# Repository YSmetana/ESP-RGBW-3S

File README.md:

View this project on [CADLAB.io](https://cadlab.io/project/24320). 

# ESP-RGBW-3S
## Soldering
### Special
R91-R94 used only if GPIO12-14 are using as pins which needs pull-up resistors. In this case R11-18 should not be used.

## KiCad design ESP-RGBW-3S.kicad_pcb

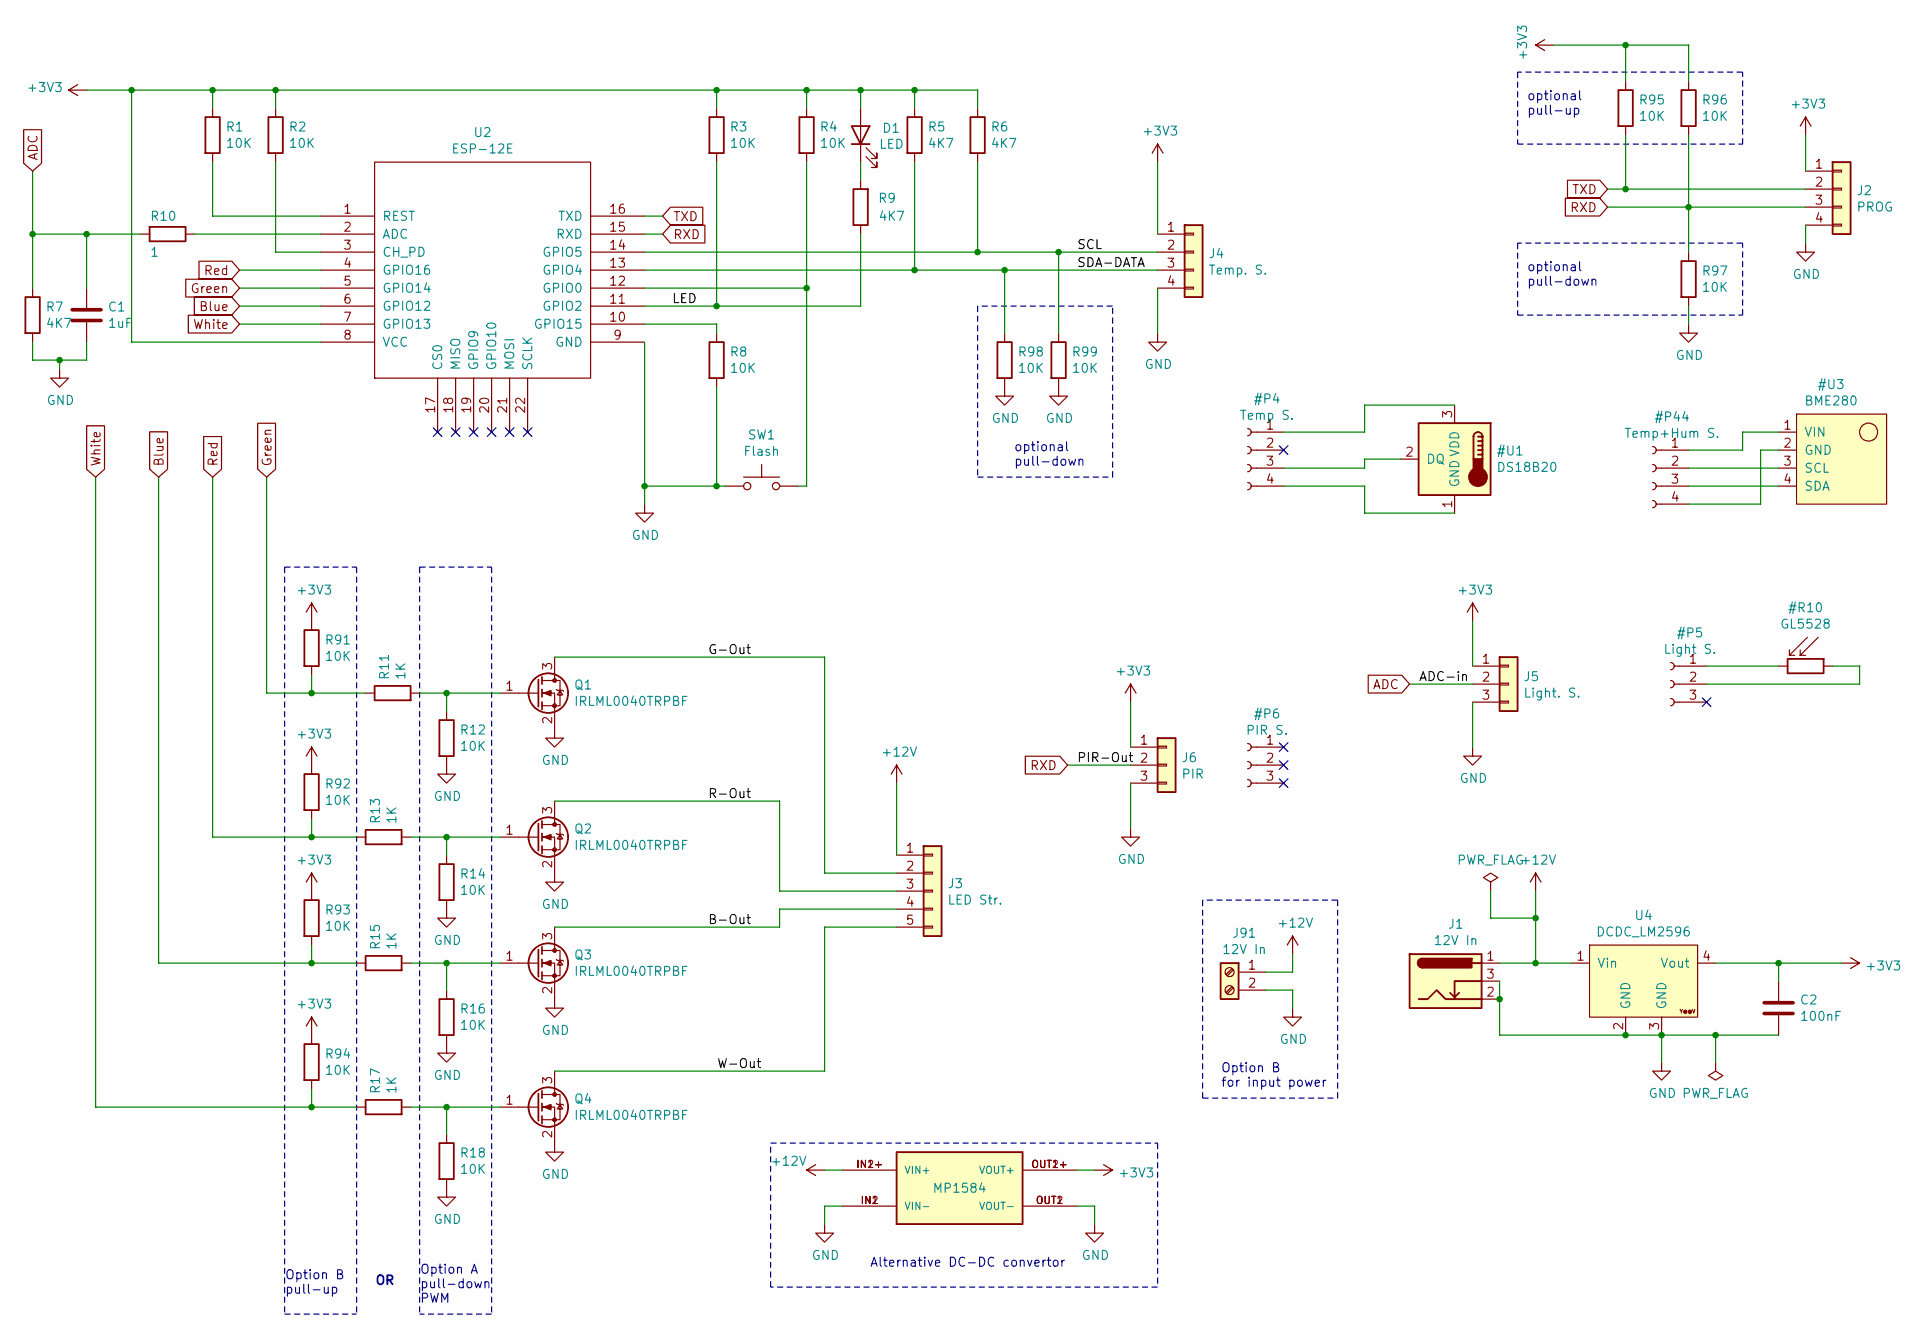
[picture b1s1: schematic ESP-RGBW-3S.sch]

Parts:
C1: 1uF; C_0805_2012Metric
C2: 100nF; C_0805_2012Metric
D1: LED; LED_D1.8mm_W3.3mm_H2.4mm
J1: 12V In; BarrelJack_Horizontal
J2: PROG; PinHeader_1x04_P2.54mm_Vertical
J3: LED Str.; Molex_KK-254_AE-6410-05A_1x05_P2.54mm_Vertical
J4: Temp. S.; Molex_KK-254_AE-6410-04A_1x04_P2.54mm_Vertical
J5: Light. S.; Molex_KK-254_AE-6410-03A_1x03_P2.54mm_Vertical
J6: PIR; Molex_KK-254_AE-6410-03A_1x03_P2.54mm_Vertical
J91: 12V In; TerminalBlock_Phoenix_MKDS-1,5-2_1x02_P5.00mm_Horizontal
Q1, Q2, Q3, Q4: IRLML0040TRPBF; SOT-23
R1, R2, R3, R4, R8, R12, R14, R16, R18, R91, R92, R93, R94, R95, R96, R97, R98, R99: 10K; R_0805_2012Metric
R5, R6, R7, R9: 4K7; R_0805_2012Metric
R10: 1; R_0805_2012Metric
R11, R13, R15, R17: 1K; R_0805_2012Metric
SW1: Flash; SW_Push_SPST_NO_Alps_SKRK
U2: ESP-12E; ESP-12E_SMD
U4: DCDC_LM2596; YAAJ_DCDC_StepDown_LM2596
U94: MP1584; DC-BRICK

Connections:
+3V3: C2.1, D1.2 (A), J2.1, J4.1, J5.1, J6.1, R1.1, R2.1, R3.1, R4.1, R5.1, R6.1, R91.1, R92.1, R93.1, R94.1, R95.1, R96.1, U2.8 (VCC), U4.4 (Vout), U94.OUT1+ (VOUT+), U94.OUT2+ (VOUT+)
+12V: J1.1, J3.1, J91.1, U4.1 (Vin), U94.IN1+ (VIN+), U94.IN2+ (VIN+)
/B-Out: J3.4, Q3.3 (D)
/G-Out: J3.2, Q1.3 (D)
/LED: R3.2, R9.1, U2.11 (GPIO2)
/R-Out: J3.3, Q2.3 (D)
/SCL: J4.2, R6.2, R99.1, U2.14 (GPIO5)
/SDA-DATA: J4.3, R5.2, R98.1, U2.13 (GPIO4)
/W-Out: J3.5, Q4.3 (D)
ADC: C1.1, J5.2, R7.1, R10.2
Blue: R15.1, R93.2, U2.6 (GPIO12)
GND: C1.2, C2.2, J1.2, J1.3, J2.4, J4.4, J5.3, J6.3, J91.2, Q1.2 (S), Q2.2 (S), Q3.2 (S), Q4.2 (S), R7.2, R8.2, R12.2, R14.2, R16.2, R18.2, R97.2, R98.2, R99.2, SW1.1, U2.9 (GND), U4.2 (GND), U4.3 (GND), U94.IN1 (VIN-), U94.IN2 (VIN-), U94.OUT1 (VOUT-), U94.OUT2 (VOUT-)
Green: R11.1, R91.2, U2.5 (GPIO14)
unnamed: D1.1 (K), R9.2
unnamed: Q1.1 (G), R11.2, R12.1
unnamed: Q2.1 (G), R13.2, R14.1
unnamed: Q3.1 (G), R15.2, R16.1
unnamed: Q4.1 (G), R17.2, R18.1
unnamed: R1.2, U2.1 (REST)
unnamed: R2.2, U2.3 (CH_PD)
unnamed: R4.2, SW1.2, U2.12 (GPIO0)
unnamed: R8.1, U2.10 (GPIO15)
unnamed: R10.1, U2.2 (ADC)
RXD: J2.3, J6.2, R96.2, R97.1, U2.15 (RXD)
Red: R13.1, R92.2, U2.4 (GPIO16)
TXD: J2.2, R95.2, U2.16 (TXD)
White: R17.1, R94.2, U2.7 (GPIO13)

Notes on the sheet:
Option A pull-down PWM
Option B pull-up
optional pull-up
optional pull-down
Option B for input power
Alternative DC-DC convertor

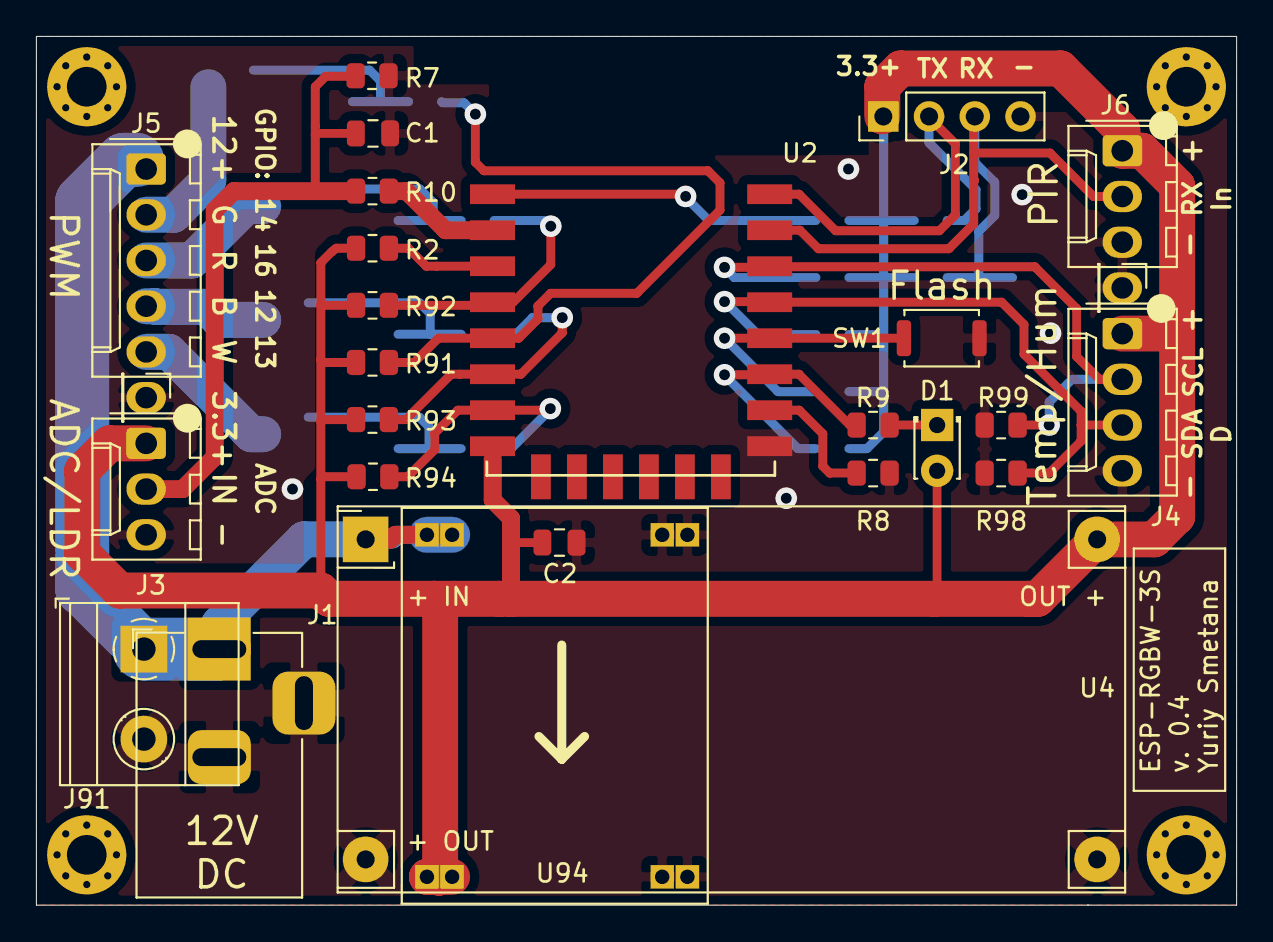
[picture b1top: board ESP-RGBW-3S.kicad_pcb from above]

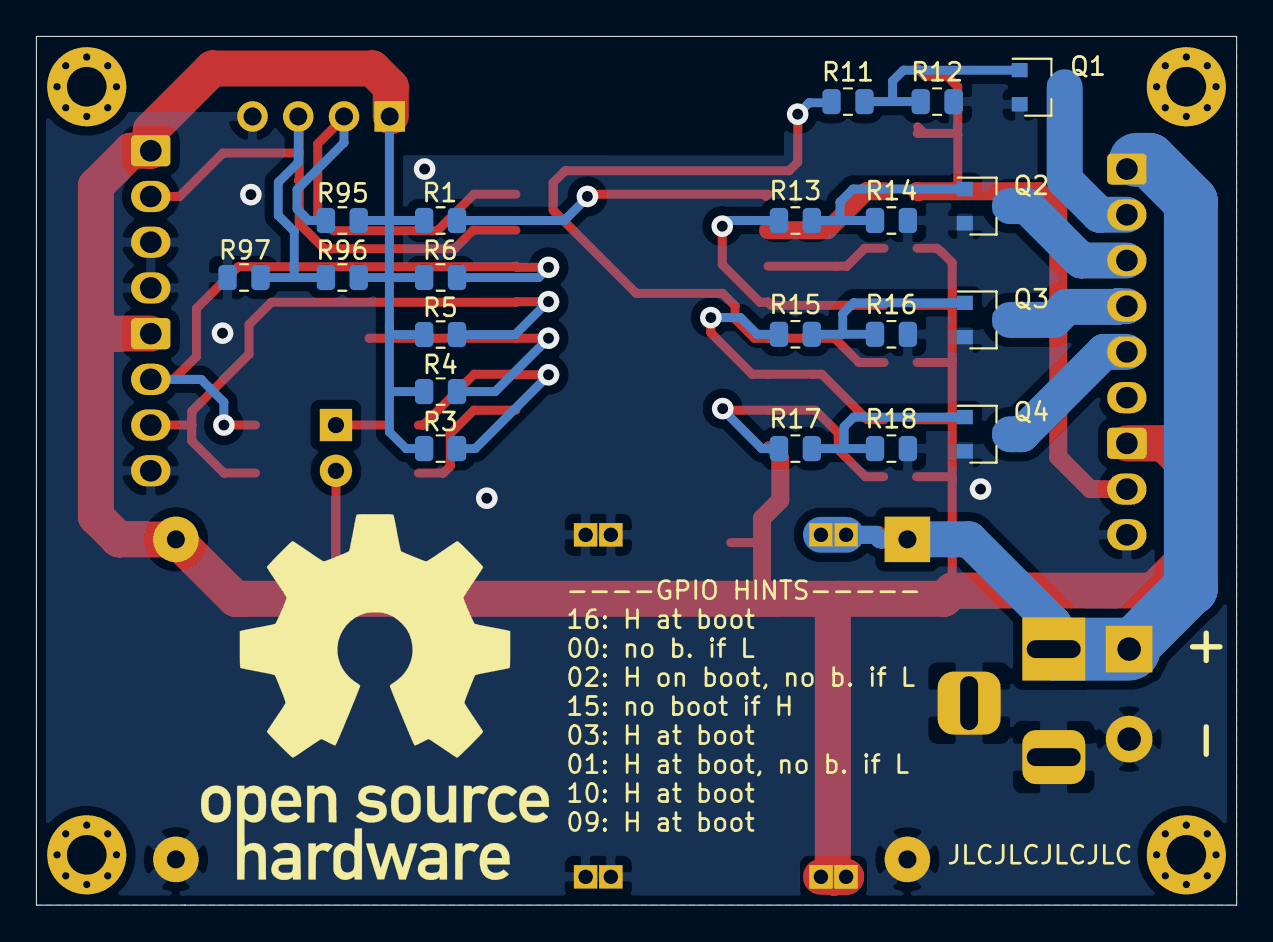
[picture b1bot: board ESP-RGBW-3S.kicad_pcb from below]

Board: 2 copper layers, 66.7 x 48.3 mm, 46 parts (21 on the bottom side), 27 nets.

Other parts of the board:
IMG1: LOGO; open-hardware-logo

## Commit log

2021-05-18 v 0.1
2021-05-18 Backlink to CADLAB.io has been added.
2021-05-18 v 0.2
2021-05-19 GPIO15 as Red ch. output instead of TX
2021-05-20 extra GND pin next to PWM
2021-05-20 key marks for connectors
2021-05-20 silc correction, optional extra GND for J6
2021-05-20 v 0.4, pull-up option for GPIO 12-14
2021-05-20 Create fp-lib-table
2021-05-23 pull-up resistors for GPIO 12-16 reposition
2021-05-23 optional pull-up and pull-down resistors for TX-RX
2021-05-24 oprional pull-down resistors for GPIO 4-5
2021-05-24 bottom resistors realigment
2021-05-29 oprional input power terminal
2021-05-29 open hardware logo
2021-05-29 alternative DC-DC convertor (MP1584)
2021-05-30 status LED controlled by low-velef on mcu pin
2021-05-30 some hints on silk layer
2021-05-30 silk layer
2021-06-26 gerber files
